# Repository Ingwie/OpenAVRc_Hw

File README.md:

# OpenAVRc_Hw

This is the hardware / addons part of OpenAVRc.

For source code or documentation : Visit https://github.com/Ingwie/OpenAVRc_Dev

----------
**Welcome to**
=========
                 ____                ___ _   _____                      
                / __ \___  ___ ___  / _ | | / / _ \____                 
               / /_/ / _ \/ -_) _ \/ __ | |/ / , _/ __/                 
               \____/ .__/\__/_//_/_/ |_|___/_/|_|\__/                  
                   /_/                                                  
              
              =========================================
----------
## OpenAVRc Hardware and addons
1. Introduction (this page)

	You will find here all hardwares developped by the OpenAVRc Team.
	
1. OpenAVRc Shield

   This is the main board used by our [OpenAVRc project](https://github.com/Ingwie/OpenAVRc_Dev).
   * [V2.0](https://github.com/Ingwie/OpenAVRc_Hw/tree/V3/PCB%20Shield/Mega_2560%20core%20mini_full_2.0_PM) (deprecated)
   * [V2.1](https://github.com/Ingwie/OpenAVRc_Hw/tree/V3/PCB%20Shield/Mega_2560%20core%20mini_full_2.1_PM)
   * [V2.2](https://github.com/Ingwie/OpenAVRc_Hw/tree/V3/PCB%20Shield/Mega_2560%20core%20mini_full_2.2_PM) (actually under development)

1. MultiSwitch_Sw16-ProMicro
   * [V1.0](https://github.com/Ingwie/OpenAVRc_Hw/tree/V3/MultiSwitch_Sw16-ProMicro)

1. MultiSwitch_Sw8 (deprecated)
   * [V1.0](https://github.com/Ingwie/OpenAVRc_Hw/tree/V3/MultiSwitch_Sw8)

1. MultiSwitch_Sw8 V2
   * [V1.2](https://github.com/Ingwie/OpenAVRc_Hw/tree/V3/MutltiSwitch_Sw8_V2)

1. MultiSwitch_Sw8 V3
   * [V1.3](https://github.com/Ingwie/OpenAVRc_Hw/tree/V3/MultiSwitch_Sw8_V3)

1. The MS8-Xany card used as an Impulse Sequencer
   * [V1.0](https://github.com/Ingwie/OpenAVRc_Hw/tree/V3/MultiSwitch_Sw8_PulseSeq)

1. Xany2Msx
   * [V1.0](https://github.com/Ingwie/OpenAVRc_Hw/tree/V3/Xany2Msx)

1. MultiSwitch_MosFet
   * [V1.0](https://github.com/Ingwie/OpenAVRc_Hw/tree/V3/MultiSwitch_MosFet)

1. Capteur_Hall_I2C
   * [V1.0](https://github.com/Ingwie/OpenAVRc_Hw/tree/V3/Capteur_Hall_I2C)

1. Capteur_Hall_I2C Mini
   * [V1.0](https://github.com/Ingwie/OpenAVRc_Hw/tree/V3/Capteur_Hall_I2C_Mini)

1. Encoder A1335 I2C
   * [V1.0](https://github.com/Ingwie/OpenAVRc_Hw/tree/V3/PCB%20A1335_Encoder)

1. Alimentation for Mpx 3010
   * [V1.0](https://github.com/Ingwie/OpenAVRc_Hw/tree/V3/PCB%20Mpx%20Alimentation)

1. LM386 amplifier
   * [V1.0](https://github.com/Ingwie/OpenAVRc_Hw/tree/V3/PCB%20LM386%20amplifier)

1. Shield for JQ6500-28P/PAM8302
   * [V1.0](https://github.com/Ingwie/OpenAVRc_Hw/tree/V3/PCB%20JQ6500-28P_PAM8302A)

1. PAM8302 Amplifier
   * [V1.0](https://github.com/Ingwie/OpenAVRc_Hw/tree/V3/PCB%20PAM8302A)

1. Long Range hardwares solutions  
	<table cellspacing=0>
	  <tr>
		<td align=center width=200><br><b>MultiProtocol&Lora</b></td>
		<td align=center width=200><br><b>ExpressLrs</b></td>
		<td align=center width=200><br><b>Crossfire_TBS</b></td>
	  </tr>
	</table>
 
1. Xany2Sounds
   * [V1.0](https://github.com/Ingwie/OpenAVRc_Hw/tree/V3/Xany2Sounds)

1. Sound&SmokeModule
   * [V1.1](https://github.com/Ingwie/OpenAVRc_Hw/tree/V3/Sound&SmokeModule)

1. Futaba FP-S148/S3003 replacement
   * [V1.0](https://github.com/Ingwie/OpenAVRc_Hw/tree/V3/LUCAS_FPS148_FS3003)

1. Interface Buttons2Xany usable with Sound&Smoke
   * [V1.0](https://github.com/Ingwie/OpenAVRc_Hw/tree/V3/Buttons2Xany)

1. Adaptator for P16 on Shield board (LCD // connector)  
   * [v1.0](https://github.com/Ingwie/OpenAVRc_Hw/tree/V3/PCB%20Shield/Adaptateur_Connecteur_20pts_shield)  

1. BURC/Xany encoder by 4 potentiometers 
   * [v1.0](https://github.com/Ingwie/OpenAVRc_Hw/tree/V3/BurcAnaTx)

1. Express LRS & OpenAVRc 
   * [v1.0](https://github.com/Ingwie/OpenAVRc_Hw/tree/V3/Long_Range/OpenAVRc_CRSF)

## Users OpenAVRc Transmitter Builds
* [Bracame Transmitter](https://github.com/Ingwie/OpenAVRc_Hw/tree/V3/User's%20OpenAVRc%20Transmitters/Bracame/README.md)
* [JPZ Transmitter](https://github.com/Ingwie/OpenAVRc_Hw/tree/V3/User's%20OpenAVRc%20Transmitters/JPZ/README.md)
* [Pyrall Transmitter](https://github.com/Ingwie/OpenAVRc_Hw/tree/V3/User's%20OpenAVRc%20Transmitters/Pyrall/README.md)
* [Antho Transmitter](https://github.com/Ingwie/OpenAVRc_Hw/tree/V3/User's%20OpenAVRc%20Transmitters/Antho/README.md)
* [Rc-Navy](https://github.com/Ingwie/OpenAVRc_Hw/tree/V3/User's%20OpenAVRc%20Transmitters/Rc-Navy/README.md)
* [Pascalou95](https://github.com/Ingwie/OpenAVRc_Hw/tree/V3/User's%20OpenAVRc%20Transmitters/Pascalou95/README.md)
* [pierrotm777 Transmitter](https://github.com/Ingwie/OpenAVRc_Hw/tree/V3/User's%20OpenAVRc%20Transmitters/pierrotm777/README.md)
* [Jirí Stanek Transmitter](https://github.com/Ingwie/OpenAVRc_Hw/tree/V3/User's%20OpenAVRc%20Transmitters/JiríStanek/README.md)
* [Jeffri Ranger Transmitters](https://github.com/Ingwie/OpenAVRc_Hw/tree/V3/User's%20OpenAVRc%20Transmitters/JeffriRanger/README.md)
* [Dhe Tattoo bandung Transmitter (with FVP feature)](https://github.com/Ingwie/OpenAVRc_Hw/tree/V3/User's%20OpenAVRc%20Transmitters/DheTattoobandung/README.md)
* [Feng Wenké Transmitter](https://github.com/Ingwie/OpenAVRc_Hw/tree/V3/User's%20OpenAVRc%20Transmitters/FengWenké/README.md)
* [Aat Tsani Transmitter](https://github.com/Ingwie/OpenAVRc_Hw/tree/V3/User's%20OpenAVRc%20Transmitters/AatTsani/README.md)
* [F1FNW Transmitter](https://github.com/Ingwie/OpenAVRc_Hw/tree/V3/User's%20OpenAVRc%20Transmitters/F1FNW/README.md)
* [guilm Transmitter](https://github.com/Ingwie/OpenAVRc_Hw/tree/V3/User's%20OpenAVRc%20Transmitters/guilm/README.md)
* [ElectoPete Transmitter](https://github.com/Ingwie/OpenAVRc_Hw/tree/V3/User's%20OpenAVRc%20Transmitters/ElectoPete/README.md)
* [seb276 Transmitter](https://github.com/Ingwie/OpenAVRc_Hw/tree/V3/User's%20OpenAVRc%20Transmitters/seb276/README.md)
* [sloped-soarer Transmitter](https://github.com/Ingwie/OpenAVRc_Hw/tree/V3/User's%20OpenAVRc%20Transmitters/sloped-soarer/README.md)
* [FernPilot Transmitter](https://github.com/Ingwie/OpenAVRc_Hw/tree/V3/User's%20OpenAVRc%20Transmitters/FernPilot/README.md)
* [ThierryRC Transmitter](https://github.com/Ingwie/OpenAVRc_Hw/tree/V3/User's%20OpenAVRc%20Transmitters/ThierryRC/README.md)
* [Ivaylo Transmitter](https://github.com/Ingwie/OpenAVRc_Hw/tree/V3/User's%20OpenAVRc%20Transmitters/Ivaylo/README.md)
* [AlessandroAU Transmitter](https://github.com/Ingwie/OpenAVRc_Hw/tree/V3/User's%20OpenAVRc%20Transmitters/AlessandroAU/README.md)
* [Abrito Transmitter](https://github.com/Ingwie/OpenAVRc_Hw/tree/V3/User's%20OpenAVRc%20Transmitters/Abrito/README.md)
* [Lestroy Transmitter](https://github.com/Ingwie/OpenAVRc_Hw/tree/V3/User's%20OpenAVRc%20Transmitters/Lestroy/README.md)
* [fanqie123 Transmitter](https://github.com/Ingwie/OpenAVRc_Hw/tree/V3/User's%20OpenAVRc%20Transmitters/fanqie123/README.md)
* [LuizMaia Transmitter](https://github.com/Ingwie/OpenAVRc_Hw/tree/V3/User's%20OpenAVRc%20Transmitters/LuizMaia/README.md)
* [Dogtag Transmitter](https://github.com/Ingwie/OpenAVRc_Hw/tree/V3/User's%20OpenAVRc%20Transmitters/Dogtag/README.md)
* [Olc Transmitter](https://github.com/Ingwie/OpenAVRc_Hw/tree/V3/User's%20OpenAVRc%20Transmitters/Olc/README.md)
* [Croky_b Transmitter](https://github.com/Ingwie/OpenAVRc_Hw/tree/V3/User's%20OpenAVRc%20Transmitters/Croky_b/README.md)
* [Munir Ahmad Transmitter](https://github.com/Ingwie/OpenAVRc_Hw/tree/V3/User's%20OpenAVRc%20Transmitters/MunirAhmad/README.md)

## Users Builds with X-Any
* [Xany by Rc-Navy](https://github.com/Ingwie/OpenAVRc_Hw/tree/V3/Xany_Builds_by_Users/Rc-Navy)
* [Xany by JPZ](https://github.com/Ingwie/OpenAVRc_Hw/tree/V3/Xany_Builds_by_Users/JPZ)
* [Xany by pierrotm777](https://github.com/Ingwie/OpenAVRc_Hw/tree/V3/Xany_Builds_by_Users/pierrotm777)
* [Xany by Pyrall](https://github.com/Ingwie/OpenAVRc_Hw/tree/V3/Xany_Builds_by_Users/Pyrall)

## Users Builds with Bluetooth feature
These modules use the **OpenAVRc Blutooth** feature
   An **OpenAVRc** transmitter can be connected to another **OpenAVRc** transmitter for schooling mode.  
   One use the master role and the other the slave role.  
   But it's also possible to use this Bluetooth feature for these three projects:    
   This Bluetooth mode can be used for use an external Joystick for command the transmitter or use a Head Tracker for FPV or replace PPM cable for use with a simulator.
   Replace transmitter stick by a joystick **Logitech 3D Pro**:  
     * [OpenAVRcBT_JoystickReader](https://github.com/Ingwie/OpenAVRc_Hw/tree/V3/Bluetooth/OpenAVRcBT_JoystickReader)  
   Use your transmitter with simulator (**CPPM** or **joystick** modes):   
     * [OpenAVRcBT_ToSimulator](https://github.com/Ingwie/OpenAVRc_Hw/tree/V3/Bluetooth/OpenAVRcBT_ToSimulator)  
   Command camera and more:  
     * [OpenAVRcBT_HeadTrackerFW](https://github.com/Ingwie/OpenAVRc_Hw/tree/V3/Bluetooth/OpenAVRcBT_HeadTrackerFW)  
  
----------

   OpenAVRc is free software: you can redistribute it and/or modify    
   it under the terms of the GNU General Public License as published    
   by the Free Software Foundation, either version 2 of the License,   
   or (at your option) any later version.

   OpenAVRc is distributed in the hope that it will be useful,         
   but WITHOUT ANY WARRANTY; without even the implied warranty of       
   MERCHANTABILITY or FITNESS FOR A PARTICULAR PURPOSE.  See the        
   GNU General Public License for more details.                         
                                                                        
>        License GPLv2: http://www.gnu.org/licenses/gpl-2.0.html          

----------

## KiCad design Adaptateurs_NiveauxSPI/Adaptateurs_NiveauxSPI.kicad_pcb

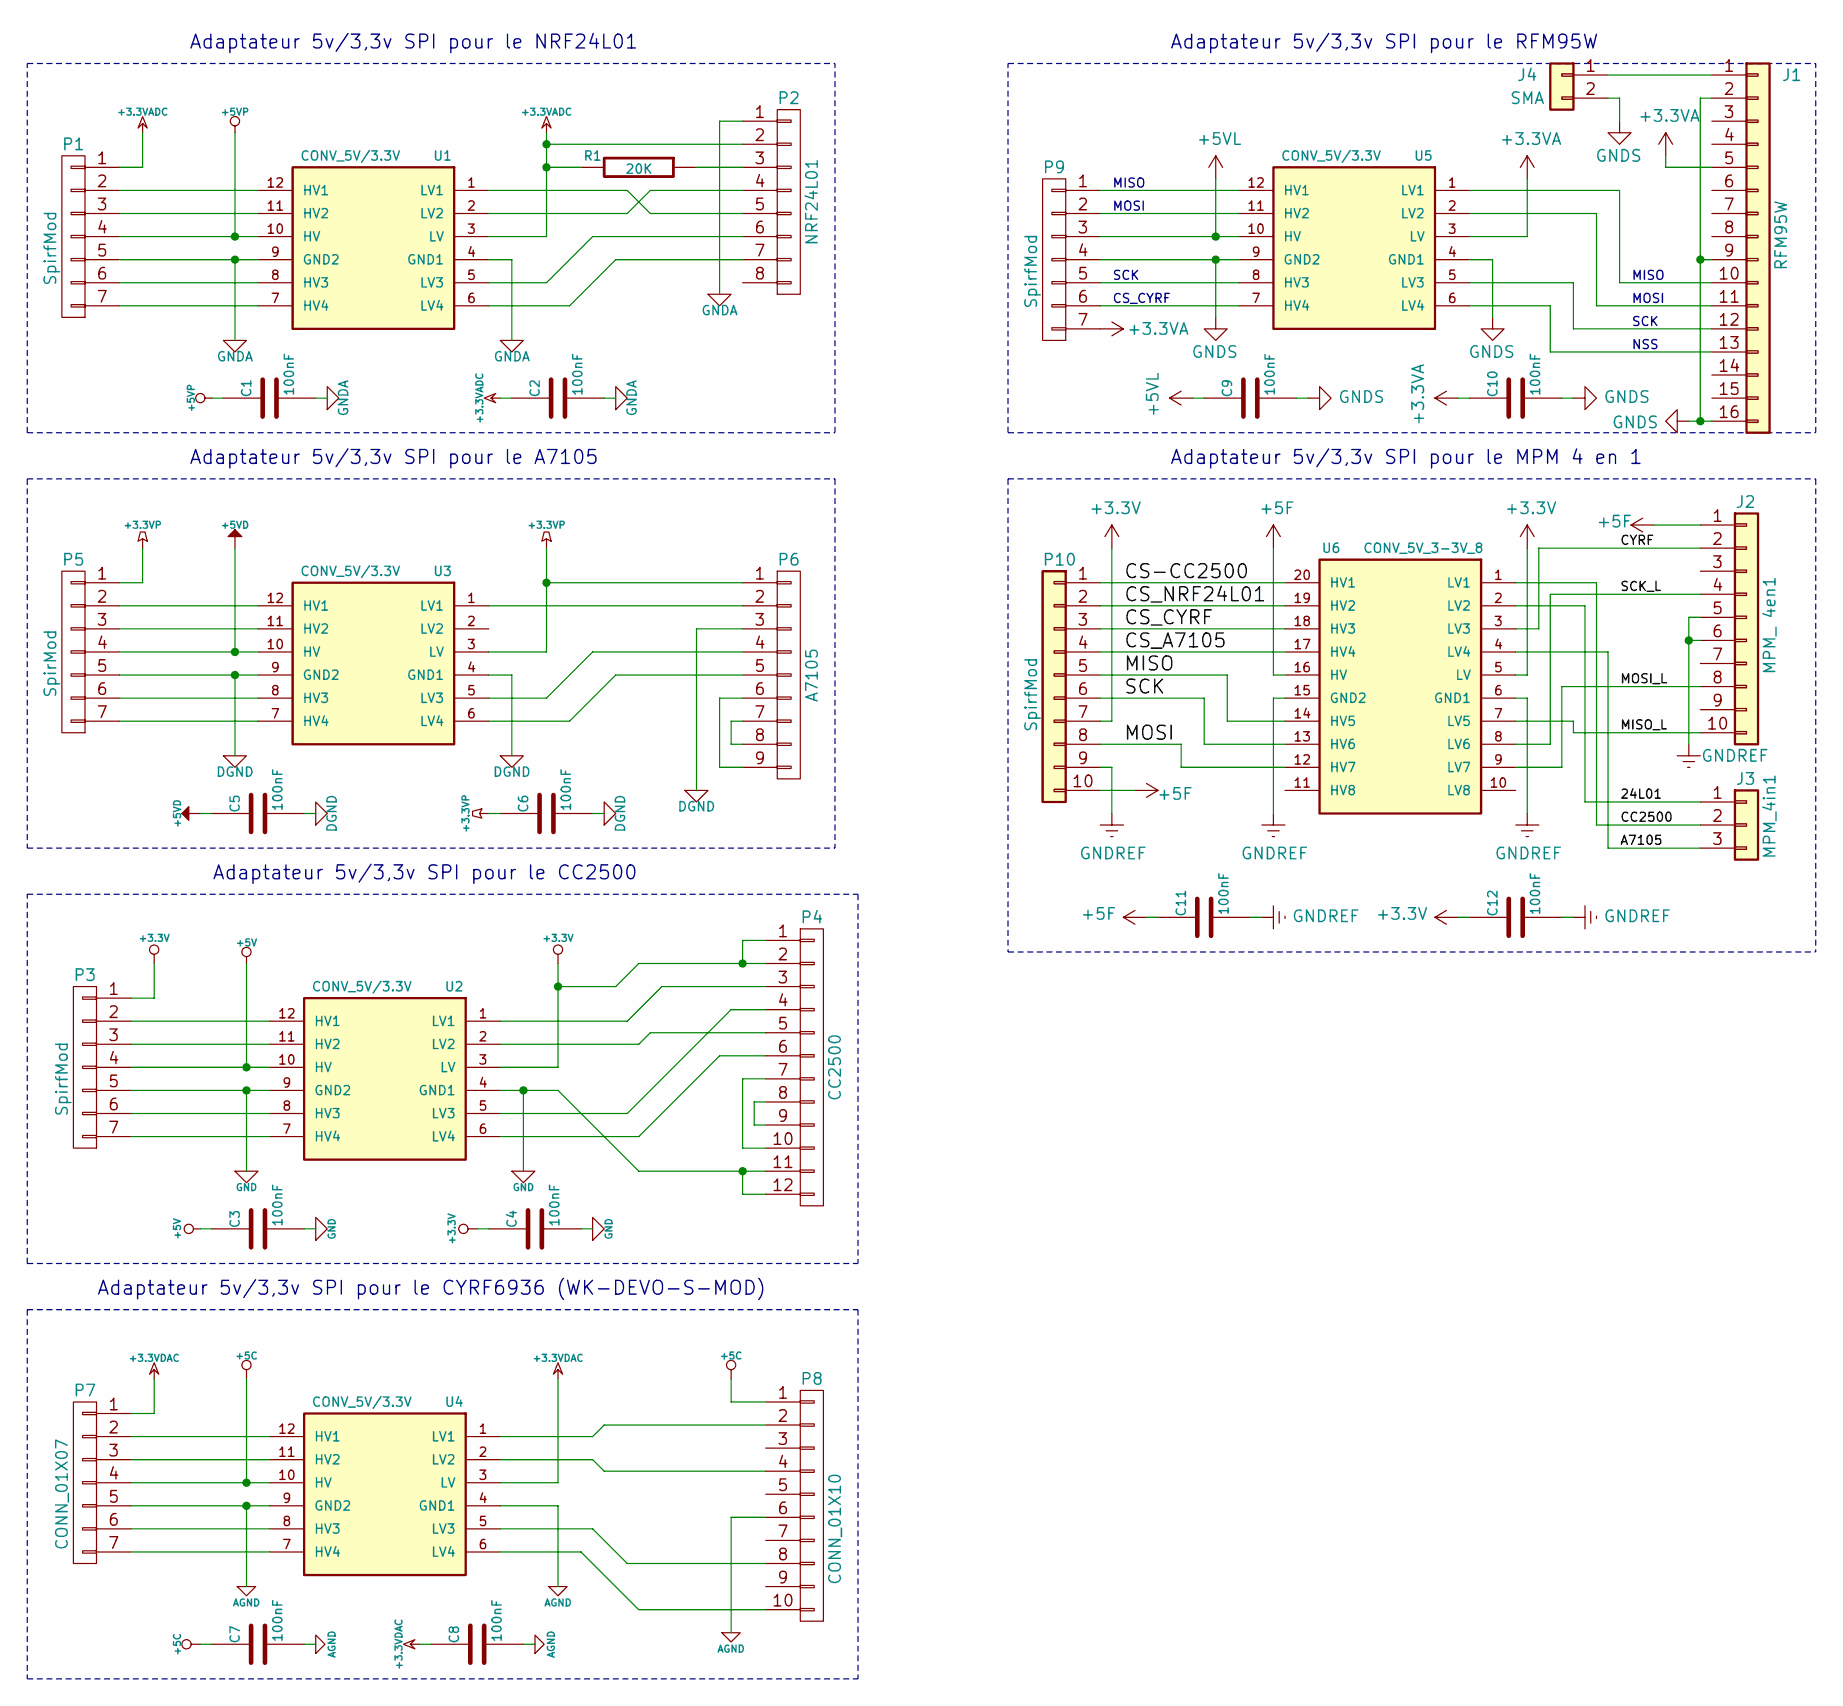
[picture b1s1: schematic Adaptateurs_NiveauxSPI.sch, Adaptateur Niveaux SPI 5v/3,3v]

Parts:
C1, C2, C3, C4, C5, C6, C7, C8, C9, C10, C11, C12: 100nF; C_1206_3216Metric_Pad1.42x1.75mm_HandSolder
J1: RFM95W
J2: MPM_ 4en1; PinHeader_2x05_P2.00mm_Vertical
J3: MPM_4in1; PinHeader_1x03_P2.54mm_Vertical
J4: SMA; SMA_Amphenol_132289_EdgeMount
P1, P3, P9: SpirfMod; PinHeader_1x07_P2.54mm_Vertical
P2: NRF24L01; PinHeader_2x04_P2.54mm_Vertical
P4: CC2500; PinHeader_2x06_P2.54mm_Vertical
P5: SpirMod; PinHeader_1x07_P2.54mm_Vertical
P6: A7105; Pin_Header_Straight_1x09_Pitch2mm
P7: CONN_01X07; PinHeader_1x07_P2.54mm_Vertical
P8: CONN_01X10; PinHeader_2x05_P2.54mm_Vertical
P10: SpirfMod; PinHeader_2x05_P2.54mm_Vertical
R1: 20K; R_1206_3216Metric_Pad1.42x1.75mm_HandSolder
U1, U2, U3, U4: CONV_5V/3.3V; Level_Convertissor_W10.16mm
U5: CONV_5V/3.3V; Level_Convertissor_SMD
U6: CONV_5V_3-3V_8; Level_Convertissor_8_W10.16mm

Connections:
+3.3VA: C10.1, J1.5, P9.7, U5.3 (LV)
+3.3VADC: C2.1, P1.1, P2.2, R1.2, U1.3 (LV)
+3.3VDAC: C8.1, P7.1, U4.3 (LV)
+3.3VP: C6.1, P5.1, P6.1, U3.3 (LV)
+5C: C7.1, P7.4, P8.1, U4.10 (HV)
+5F: C11.1, J2.1, P10.10, U6.16 (HV)
+5V: C3.1, P3.4, U2.10 (HV)
+5VD: C5.1, P5.4, U3.10 (HV)
+5VL: C9.1, P9.3, U5.10 (HV)
+5VP: C1.1, P1.4, U1.10 (HV)
/24L01: J3.1, U6.2 (LV2)
/A7105: J3.3, U6.4 (LV4)
/CC2500: J3.2, U6.1 (LV1)
/CS-CC2500: P10.1, U6.20 (HV1)
/CS_A7105: P10.4, U6.17 (HV4)
/CS_CYRF: P10.3, U6.18 (HV3)
/CS_NRF24L01: P10.2, U6.19 (HV2)
/CYRF: J2.2, U6.3 (LV3)
/MISO: P10.5, U6.14 (HV5)
/MISO_L: J2.10, U6.7 (LV5)
/MOSI: P10.8, U6.12 (HV7)
/MOSI_L: J2.8, U6.9 (LV7)
/SCK: P10.6, U6.13 (HV6)
/SCK_L: J2.4, U6.8 (LV6)
AGND: C7.2, C8.2, P7.5, P8.6, U4.4 (GND1), U4.9 (GND2)
DGND: C5.2, C6.2, P5.5, P6.3, U3.4 (GND1), U3.9 (GND2)
GND: C3.2, C4.2, P3.5, P4.11, P4.12, U2.4 (GND1), U2.9 (GND2)
GNDA: C1.2, C2.2, P1.5, P2.1, U1.4 (GND1), U1.9 (GND2)
GNDREF: C11.2, C12.2, J2.5, J2.6, P10.9, U6.6 (GND1), U6.15 (GND2)
GNDS: C9.2, C10.2, J1.2, J1.9, J1.16, J4.2, P9.4, U5.4 (GND1), U5.9 (GND2)
unnamed: J1.1, J4.1
unnamed: J1.10, U5.1 (LV1)
unnamed: J1.11, U5.2 (LV2)
unnamed: J1.12, U5.5 (LV3)
unnamed: J1.13, U5.6 (LV4)
unnamed: P1.2, U1.12 (HV1)
unnamed: P1.3, U1.11 (HV2)
unnamed: P1.6, U1.8 (HV3)
unnamed: P1.7, U1.7 (HV4)
unnamed: P2.3, R1.1
unnamed: P2.4, U1.2 (LV2)
unnamed: P2.5, U1.1 (LV1)
unnamed: P2.6, U1.5 (LV3)
unnamed: P2.7, U1.6 (LV4)
unnamed: P3.2, U2.12 (HV1)
unnamed: P3.3, U2.11 (HV2)
unnamed: P3.6, U2.8 (HV3)
unnamed: P3.7, U2.7 (HV4)
unnamed: P4.3, U2.1 (LV1)
unnamed: P4.4, U2.5 (LV3)
unnamed: P4.5, U2.2 (LV2)
unnamed: P4.6, U2.6 (LV4)
unnamed: P4.8, P4.9
unnamed: P4.7, P4.10
unnamed: P5.2, U3.12 (HV1)
unnamed: P5.3, U3.11 (HV2)
unnamed: P5.6, U3.8 (HV3)
unnamed: P5.7, U3.7 (HV4)
unnamed: P6.2, U3.1 (LV1)
unnamed: P6.4, U3.5 (LV3)
unnamed: P6.5, U3.6 (LV4)
unnamed: P6.6, P6.9
unnamed: P6.7, P6.8
unnamed: P7.2, U4.12 (HV1)
unnamed: P7.3, U4.11 (HV2)
unnamed: P7.6, U4.8 (HV3)
unnamed: P7.7, U4.7 (HV4)
unnamed: P8.2, U4.1 (LV1)
unnamed: P8.4, U4.2 (LV2)
unnamed: P8.8, U4.5 (LV3)
unnamed: P8.10, U4.6 (LV4)
unnamed: P9.1, U5.12 (HV1)
unnamed: P9.2, U5.11 (HV2)
unnamed: P9.5, U5.8 (HV3)
unnamed: P9.6, U5.7 (HV4)

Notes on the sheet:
Adaptateur 5v/3,3v SPI pour le CYRF6936 (WK-DEVO-S-MOD)
Adaptateur 5v/3,3v SPI pour le CC2500
Adaptateur 5v/3,3v SPI pour le NRF24L01
Adaptateur 5v/3,3v SPI pour le A7105
Adaptateur 5v/3,3v SPI pour le RFM95W
Adaptateur 5v/3,3v SPI pour le MPM 4 en 1
NSS
SCK
MOSI
MISO
CS_CYRF

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
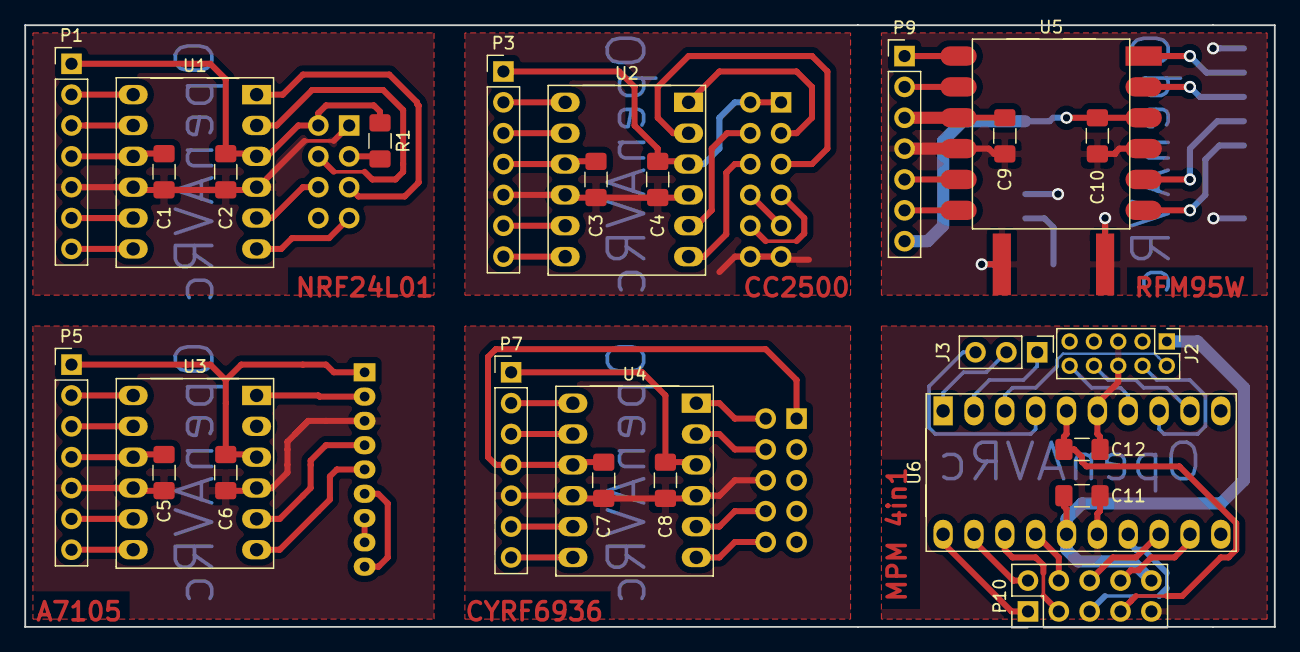
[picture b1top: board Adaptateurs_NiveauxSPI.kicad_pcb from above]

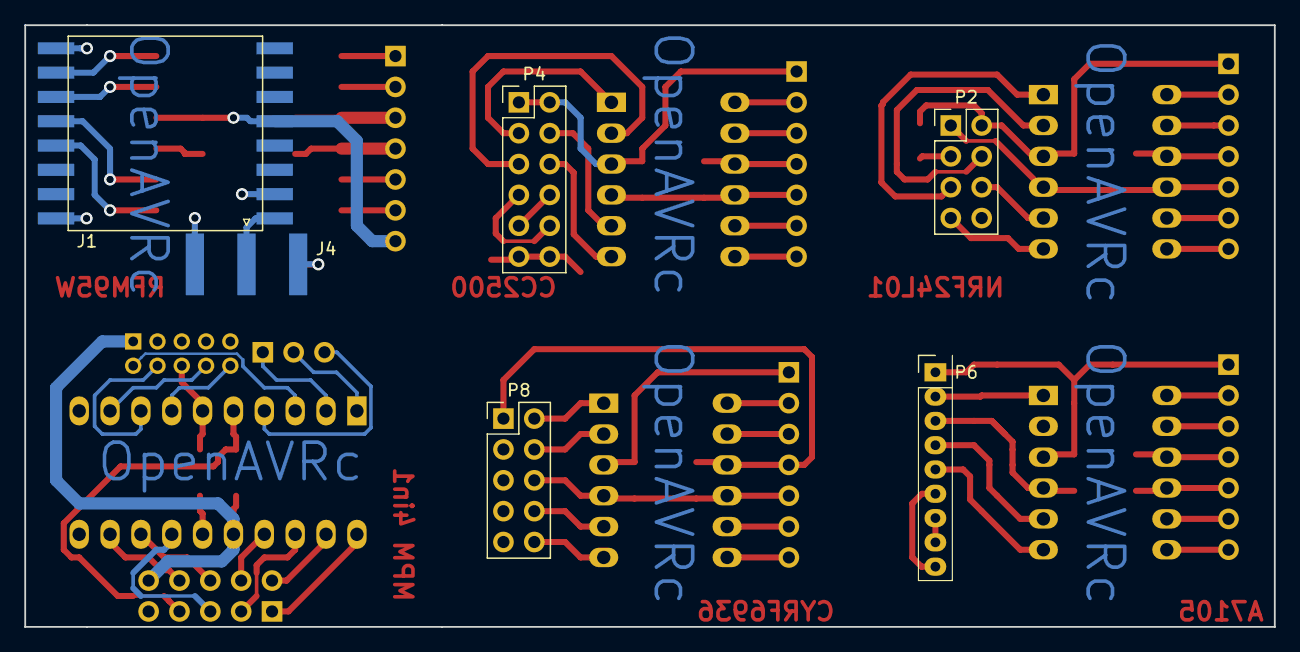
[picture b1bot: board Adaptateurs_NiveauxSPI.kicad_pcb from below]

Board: 2 copper layers, 102.9 x 49.5 mm, 33 parts (6 on the bottom side), 77 nets.

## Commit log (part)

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2022-12-17 Update README.md
    Replace ppmEncoder by TinyCppmGen into Readme file
2022-12-17 Update schematics files
    PPM output use the PIN3.
2022-12-17 Update Schema_Mega_2560 core mini_full_v2.2.pdf
    Update v2.2 shield (SCC = P27)
2022-12-17 Update Mega_2560 core mini_full_2.2-KICAD.zip
    Update zip kicad file
2022-12-29 Delete ShieldV2.0.doc
    remove old doc
2023-04-10 Add Kicad & gerber files
2023-05-05 Add Ms8 V2
2023-05-05 Add pictures
2023-05-05 Add Ms8 V2 into main Readme.md file
2023-05-05 change pic sizes
2023-05-06 Update
    - Add documentation V2
    - Add firmware V2
2023-05-06 Add Croky_b transmitter
2023-05-06 Add T1 T2
2023-05-29 Update firmware & doc
    Solve SBUS protocol issue
    Add Push button feature
2023-07-26 Add Munir Ahmad videos
2023-07-26 solve MunirAhmad link issue
2023-10-24 Create Futaba FP-S148 board replacement
2023-10-24 Update Readme files
2023-10-24 Add schematic file
2023-10-24 add schottle motor example
2023-10-25 Update as5600 position
2023-11-11 Change folder's name
2023-11-11 Update README.md
    Oups !
2023-11-20 update schematic
2023-12-05 Add new PCB for A1335 hall sensor
2024-01-02 Add docs
2024-01-04 Change PulseSeq version's name
2024-01-21 Add firmwares
2024-01-21 Add fuses values
2024-02-18 Add
    - Add Sound&Smoke commandes.
    - Add Beier commandes
2024-02-18 Update sounds
2024-02-20 Update Goose's sound and Readme
2024-02-20 Update README.md
    - replace tab by spaces
2024-03-02 Update README.md
    update sound&smoke commandes list to v0.2
2024-03-17 Add manual
2024-03-17 Change version to v1.1
2024-06-25 some adds
2024-07-10 Update Xany2Msx manual
2024-07-15 Update Xany2Msx firmware
    - update Graupner code
2024-07-28 Update to v0.4
    Solve Multiplex receiver issue by add option F=X
2024-10-21 Several updates
2024-10-26 Add buttons option into documentation
2024-11-02 Update doc
    Add 8 buttons option
2024-11-18 Add first doc
2024-12-25 Create Buttons2Xany
2024-12-25 modify readme
2024-12-25 Add pdf manual file
2024-12-25 update pdf file
2024-12-26 remove txt file add fuses
2024-12-26 update buttons2xany manual
2025-01-04 Add buttons keyboard infos
2025-02-25 Update to v1.1 version
    - Add HM10 for EdgeTx or OpenTx compatibility
    - Update Cppm option with new lib
    - Add Sbus feature
2025-02-25 Add software and lib
2025-05-08 update buttons mode
2025-11-24 Update Ms8 v2 firmware to v2.1
    Solve several issues
2025-11-30 Rename MultiSwitch Ms8 V2
2025-11-30 Create Ms8 V3 backup
2025-11-30 rename schematic file
2025-11-30 Add jpg pcb files
2025-12-01 Mise à jour doc
2025-12-06 update readme file
    Add upload firmware instructions.
2025-12-07 add pcb kicad files and gerber
2025-12-19 Update doc
2025-12-21 Add EKMFA firmware
    Thanks Philippe !!!!!
2025-12-24 Some changes
    - Add v1.0 backup
    - Create folders v1.0 and v1.1
2025-12-24 move firmware v1.0 to v1.0 folder
2025-12-24 add top and bottom pictures
2025-12-24 Move sounds to Sounds folder
2025-12-24 move firmware folder
2025-12-24 Update
    add first v
2025-12-30 Mini Nano mod
2025-12-30 change pictures sizes
2025-12-30 add cut wire on bottom side
2025-12-30 add v3 commands
2025-12-31 add rc2
2026-01-03 Add RC3 firmware, remove Nano modifications
2026-01-03 Update doc and move input to D11
2026-01-09 Update
    Change Input RC pin to D11
2026-01-22 Create HC-05 replacement by ESP32C3
2026-01-25 Update backups shield
2026-01-26 Update with new code v1.7
    Software:
    - Slave scan is ok
    - Keep Slave's name
    - add several debug modes (tf stream count)
    Hardware:
    - Test with v2.0 et v2.1 board esp32 power by replacing bss84 with oa3401
2026-01-29 New update v1.7j
    For simulate the frame send from SLAVE to MASTER, I have added several features:
    - sg command, slave simulate slave transmitter frame and send over ESPNOW to MASTER.
    - mg command, master simulate slave frame.
    - diag tf and link command for checks status and more
    With these options, I was able to confirm the correct transfer of data from the student radio to the master radio, now I can see the BT logo on the TRAINER screen.
2026-01-29 Add new little board
    This PCB can be used to reverse the even and odd lines of the P16 connector on the shield used to connect an LCD screen in parallel.
2026-01-29 add 3d picture
2026-01-30 New update
    Goods news !
    - The connection between the two radios is now active, and the student radio's sticks are correctly displayed on the master radio's training screen with the BT logo !
    The last version is the v1.7mfix.
    - I also had a power supply issue with the Bluetooth module and therefore the ESP32 via the BSS84 MOSFET. After replacing it with an OA3401, the component is now perfectly powered.
2026-02-01 New update
    Added several options:
    - Connection with a transmitter other than OpenAVRc in PPM or SBUS modes
    - Add md files (architecture, design's choices etc...)
2026-02-05 Create hardware PCB JR bay for espnow simulator
2026-02-05 add readme file
2026-02-05 remove
2026-02-05 Create first shield upgrade
2026-02-05 adds
2026-02-05 remove files
2026-02-05 Add external bouton scan for master only
2026-02-06 Update all md files
2026-02-06 rename
2026-02-06 create new md files
2026-02-06 move /rename files
2026-02-08 update v3
2026-02-08 update hc05 connectors
2026-02-08 add compilation bt option
2026-02-08 replace picture
2026-02-08 Adds
    - Update MS8 V3 documentation
    - Update Xany/Rcul tests
2026-02-11 add libraries for compile esp32 code.
2026-02-11 rename files and updates
2026-02-12 add wifi code into specifics tabs
2026-02-13 Update ESPNOW_Trainer.png
    External led use pin 9.
2026-02-13 Update libraries.zip
    Update ESP32_PPM lib and add Rcul lib
2026-02-13 add R5/R6 pcb update
2026-02-13 update size pictures
2026-02-14 updates MS8 and BT
2026-02-14 add espota.exe file
2026-02-16 Update to V3.2
    With this new version, it is possible to connect 2 MS8-Xany V3s (via a Y-cable) on the same RC signal provided that
    the RCUL/X-Any message carries at least 2 blocks of 8 switches.
2026-02-16 add wifi performance
2026-02-16 add results performance
2026-02-20 Add Joystick_Reader.md file
2026-02-20 update shields v2.0 and v2.1 mods
2026-02-22 update v1.8i
    Add Joystick Logitech 3D Pro as Slave only
2026-02-22 add OTG infos
2026-02-24 Update software to v1.8k
    - add logos
    - add RGB led feature for ESP32S3
2026-02-27 Adds
    - Add first doc (in french)
    - Add PCB Kicad
    -Add gerber
2026-02-27 Add schematic
2026-03-17 update firmaware
2026-03-17 Update v1.8m
    remove to many prints during STA mode.
2026-03-18 update pics
2026-03-21 update to v3.1 pcb
2026-03-21 Update 3d pictures
2026-03-21 update help into readme file
2026-03-21 Create LUCAS_FPS148_FS3003.zip
    Add new v1.2 version
2026-03-22 save LUCAS v1.2 files
2026-03-25 Add Joystick infos
2026-03-25 update joystick files
2026-03-29 update rcul/xany table
2026-04-02 Create ESP32C3_S3_HC05_v1_8p.zip
    Add just dellink, delprefs and Home Channel info
2026-04-02 add v1.1 version
2026-04-11 New firmware versuin 3.4 rc1
    Add A8 option
2026-04-14 Add several upload modes
    - add ESP32 loader mode
2026-04-14 add md files
2026-04-16 Add v1.2 with 18w amplifier audio
2026-04-17 rename hardware details to openavrc update
2026-04-17 update upload methods
2026-04-18 update to v1.8r
    Solve issue on button feature.
    - short push, call scan link
    - long push, call OTA mode
2026-04-19 Update Ms8 v3 documentation with A8 new option
2026-04-28 Add XANYCTL
2026-05-07 Add Radiomaster ER8 ELRS test (2.4GHz)
